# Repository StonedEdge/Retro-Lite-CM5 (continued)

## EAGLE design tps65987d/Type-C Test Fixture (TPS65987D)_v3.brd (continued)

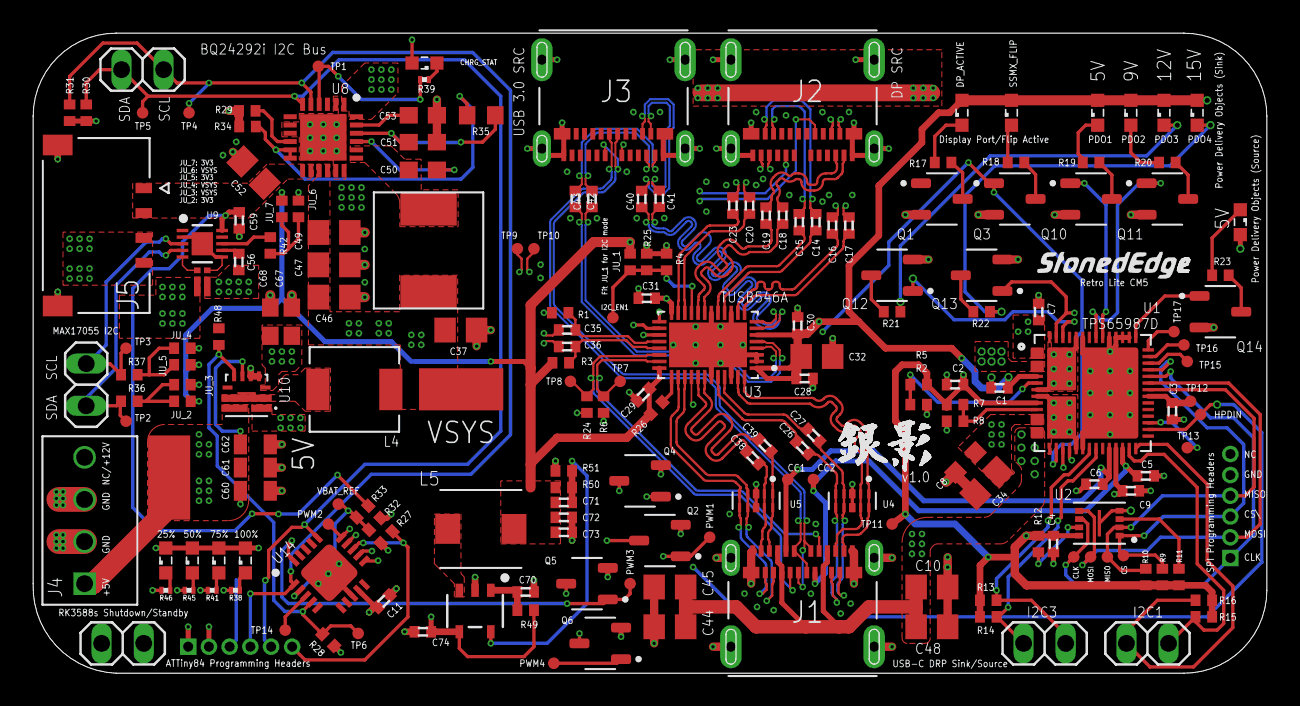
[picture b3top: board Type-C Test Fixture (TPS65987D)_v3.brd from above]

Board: 6 copper layers, 74.4 x 38.6 mm, 193 parts (0 on the bottom side), 124 nets.

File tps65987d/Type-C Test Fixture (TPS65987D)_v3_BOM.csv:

Qty,Value,Device,Package,Designator ,Description,Digikey/Mouser Link,
11,N/A,LEDSML0603,SML0603,"25%, 50%, 75%, 100%, CHRG_STAT, PDO1, PDO1_SRC1, PDO2, PDO3, PDO4, SSMX_DP_ACTIVE1",Blue LED,https://www.digikey.jp/en/products/detail/liteon/LTST-C193TB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,
5,N/A,PINHD-1X2,1X02,"JP1, JP2, JP3, JP4, JP5",PIN HEADER,https://www.digikey.jp/en/products/detail/te-connectivity-am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,
7,0 ohm,R-EU_R0402,R0402,"JU_1, JU_2, JU_3, JU_4, JU_5, JU_6, JU_7",Resistor,https://www.digikey.jp/en/products/detail/stackpole-electron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,
1,0.047µF,C-EUC0603,C0603,C50,Capacitor,https://www.digikey.jp/en/products/detail/kyocera-avx/KGM15B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,
1,0.1uF,C-EUC0402,C0402,C4,Capacitor,https://www.digikey.jp/en/products/detail/samsung-electro-me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,
3,0.1uF,C-EUC0402,C0402,"C11, C59, C70",Capacitor,https://www.digikey.jp/en/products/detail/samsung-electro-me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,
1,0.47uF,C-EUC0402,C0402,C56,Capacitor,https://www.digikey.jp/en/products/detail/samsung-electro-me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,
1,1.0uF,1.0UF-0603-16V-10%,C0603,C67,Capacitor,https://www.digikey.jp/en/products/detail/samsung-electro-me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,
2,100K,R-EU_R0402,R0402,"R1, R3",Resistor,https://www.digikey.jp/en/products/detail/yageo/RC0402FR-071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,
3,100k 1%,R-EU_R0402,R0402,"R2, R7, R8",Resistor,https://www.digikey.jp/en/products/detail/yageo/RC0402FR-071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,
18,100nF,C-EUC0402,C0402,"C14, C15, C16, C17, C18, C19, C20, C23, C28, C29, C30, C31, C35, C36, C40, C41, C42, C43",Capacitor,https://www.digikey.jp/en/products/detail/samsung-electro-me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,
1,100nF,C-EUC0402,C0402,C73,Capacitor,https://www.digikey.jp/en/products/detail/samsung-electro-me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,
1,100pF,C-EUC0402,C0402,C71,Capacitor,https://www.digikey.jp/en/products/detail/murata-electronics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,
3,N/A,105450-0101,MOLEX_105450-0101,"J1, J2, J3",USB-C Female Receptacle,https://www.digikey.jp/en/products/detail/molex/1054500101/5843890,
2,10K,R-EU_R0402,R0402,"R4, R26",Resistor,https://www.digikey.jp/en/products/detail/bourns-inc/CR0402-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,
11,10k,R-EU_R0402,R0402,"R17, R18, R19, R20, R21, R22, R23, R25, R28, R32, R49",Resistor,https://www.digikey.jp/en/products/detail/stackpole-electron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,
4,10k,R-US_R0201,R0201,"R38, R41, R45, R46",Resistor,https://www.digikey.jp/en/products/detail/stackpole-electron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,
1,10kΩ,R-EU_R0402,R0402,R34,Resistor,https://www.digikey.jp/en/products/detail/stackpole-electron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,
1,10kΩ,R-EU_R0603,R0603,R35,Resistor,,
4,10nF,C-EUC0805,C0805,"C10, C44, C45, C48",Capacitor,https://www.digikey.jp/en/products/detail/kemet/C0805X103K1R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,
1,10uF,1.0UF-0603-16V-10%,C0603,C68,Capacitor,https://www.digikey.jp/en/products/detail/samsung-electro-me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,
3,10uF,C-EUC0402,C0402,"C1, C2, C7",Capacitor,https://www.digikey.jp/en/products/detail/murata-electronics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,
2,10uF,C-EUC0402,C0402,"C72, C74",Capacitor,,
1,10uF,C-EUC0805,C0805,C32,Capacitor,,
5,10µF,C-EUC0805,C0805,"C37, C46, C47, C49, C52",Capacitor,,
1,120k 1%,R-EU_R0402,R0402,R5,Resistor,,
2,1M,R-EU_R0402,R0402,"R44, R48",Resistor,,
2,1uF,C-EUC0603,C0603,"C51, C53",Capacitor,,
1,1uH,SPM5020T-1R0M,IND_SPM5020T-1R0M,L4,Inductor,,
1,1µF,C-EUC0805,C0805,C34,Capacitor,,
1,2.2k,R-US_R0201,R0201,R39,Resistor,https://www.digikey.jp/en/products/detail/walsin-technology-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,
4,220nF,C-EUC0402,C0402,"C26, C27, C38, C39",Capacitor,,
2,220pF,C-EUC0402,C0402,"C5, C6",Capacitor,https://www.digikey.jp/en/products/detail/walsin-technology-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,
3,22uF,C-EUC0805,C0805,"C60, C61, C62",Capacitor,https://www.digikey.jp/en/products/detail/kemet/C0805C224K5R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,
1,22uF,C-EUC0402,C0402,C9,Capacitor,,
1,232k,R-EU_R0402,R0402,R50,Resistor,https://www.digikey.jp/en/products/detail/yageo/RC0402FR-072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,
1,261Ω,R-EU_R0402,R0402,R29,Resistor,https://www.digikey.jp/en/products/detail/yageo/RC0402FR-072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,
1,27.4k,R-EU_R0402,R0402,R33,Resistor,https://www.digikey.jp/en/products/detail/yageo/RC0402FR-072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,
2,2M,R-EU_R0402,R0402,"R6, R24",Resistor,https://www.digikey.jp/en/products/detail/stackpole-electron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,
4,3.3k,R-EU_R0402,R0402,"R9, R10, R11, R12",Resistor,https://www.digikey.jp/en/products/detail/walsin-technology-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,
1,332k,R-EU_R0402,R0402,R43,Resistor,https://www.digikey.jp/en/products/detail/stackpole-electron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,
10,4.7k,R-EU_R0402,R0402,"R13, R14, R15, R16, R27, R30, R31, R36, R37, R42",Resistor,https://www.digikey.jp/en/products/detail/yageo/RC0402FR-074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,
1,4.7uF,C-EUC0402,C0402,C3,Capacitor,https://www.digikey.jp/en/products/detail/samsung-electro-me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,
1,47uF,C-EUC0603,C0603,C8,Capacitor,,
1,N/A,5040500491,MOLEX_5040500491,J5,Connector,https://www.digikey.jp/en/products/detail/molex/5040500491/4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,
1,51k,R-EU_R0402,R0402,R51,Resistor,https://www.digikey.jp/en/products/detail/stackpole-electron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,
1,N/A,XIAO_4PIN_2D54,XIAO_4PIN_2D54,J4,Connector,,
2,N/A,6PINEADER,1MM_PIC-PROGRAMING_HEADER,"U$3, U$5",Programming Header,N/A,
1,AMDLA4530S-2R2MT,AMDLA4530S-2R2MT,IND_AMDLA4530S-2R2MT,L5,Inductor,https://www.digikey.jp/en/products/detail/abracon-llc/AMDLA4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,
11,N/A,AO3400A,SOT95P280X125-3N,"Q1, Q2, Q3, Q4, Q5, Q6, Q10, Q11, Q12, Q13, Q14",Transistor,https://www.digikey.jp/en/products/detail/alpha-omega-semico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,
1,N/A,ASPI-0630HI,ASPI-0630HI,L1,Inductor,https://www.digikey.jp/en/products/detail/abracon-llc/ASPI-0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,
1,N/A,BQ24292I,QFN50P400X400X100-25N,U8,Integrated Circuit,https://www.digikey.jp/en/products/detail/texas-instruments/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,
1,N/A,MAX17055ETB+T,21-100013A_T102A2+1C_MXM,U9,Integrated Circuit,https://www.digikey.jp/en/products/detail/analog-devices-inc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,
1,N/A,MCU-ATTINY84A-MU(QFN20),QFN20G-0.5-4X4MM,U14,Integrated Circuit,https://www.digikey.jp/en/products/detail/microchip-technolo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,
1,N/A,PS0306DRF7T0R01L,PS0306DRF7T0R01L,R40,,https://www.digikey.jp/en/products/detail/yageo/PS0306DRF7T0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,
1,SSMX_FLIP,LEDSML0603,SML0603,SSMX_FLIP_ACTIVE1,Blue LED,https://www.digikey.jp/en/products/detail/liteon/LTST-C193TB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,
1,SY8089AAACSY8089AAAC_SGY-L,SY8089AAACSY8089AAAC_SGY-L,SY8089AAAC_SGY-L,U13,Buck Regulator,https://www.lcsc.com/product-detail/DC-DC-Converters_Silergy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,
2,TPD4E05U06DQAR,TPD4E05U06DQAR,IC_TPD4E05U06DQAR,"U4, U5",Diode,https://www.digikey.jp/en/products/detail/texas-instruments/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,
1,TPS61235PRWLT,TPS61235PRWLT,CONV_TPS61235PRWLT,U10,Boost Regulator,https://www.digikey.jp/en/products/detail/texas-instruments/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,
1,TPS65987DDHRSHR,TPS65987DDHRSHR,IC_TPS65987DDHRSHR,U1,Integrated Circuit,https://www.digikey.jp/en/products/detail/texas-instruments/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,
1,TUSB546-DCIRNQT,TUSB546-DCIRNQT,QFN40P400X600X80-41N,U3,Integrated Circuit,https://www.digikey.jp/en/products/detail/texas-instruments/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,
1,W25X05CLUXIGTR,W25X05CLUXIGTR,PSON50P300X200X60-9N,U2,SPI Flash Memory,https://www.digikey.jp/en/products/detail/winbond-electronic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,
1,434133025816 ,434133025816 ,434133025816 ,S1,Button,,

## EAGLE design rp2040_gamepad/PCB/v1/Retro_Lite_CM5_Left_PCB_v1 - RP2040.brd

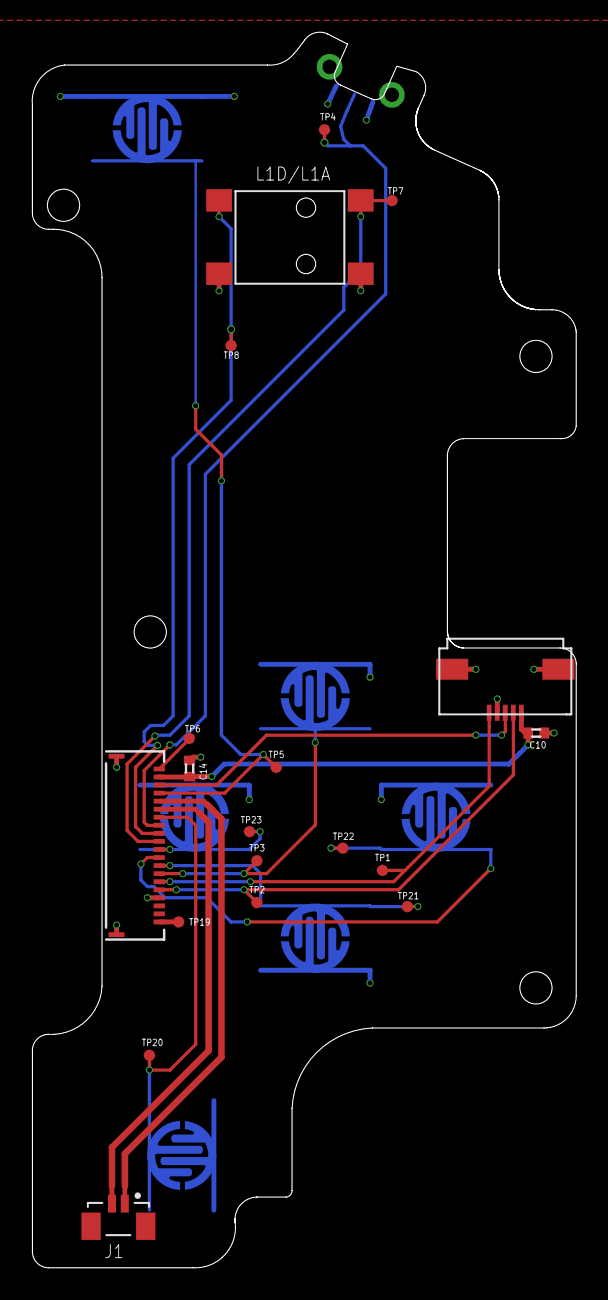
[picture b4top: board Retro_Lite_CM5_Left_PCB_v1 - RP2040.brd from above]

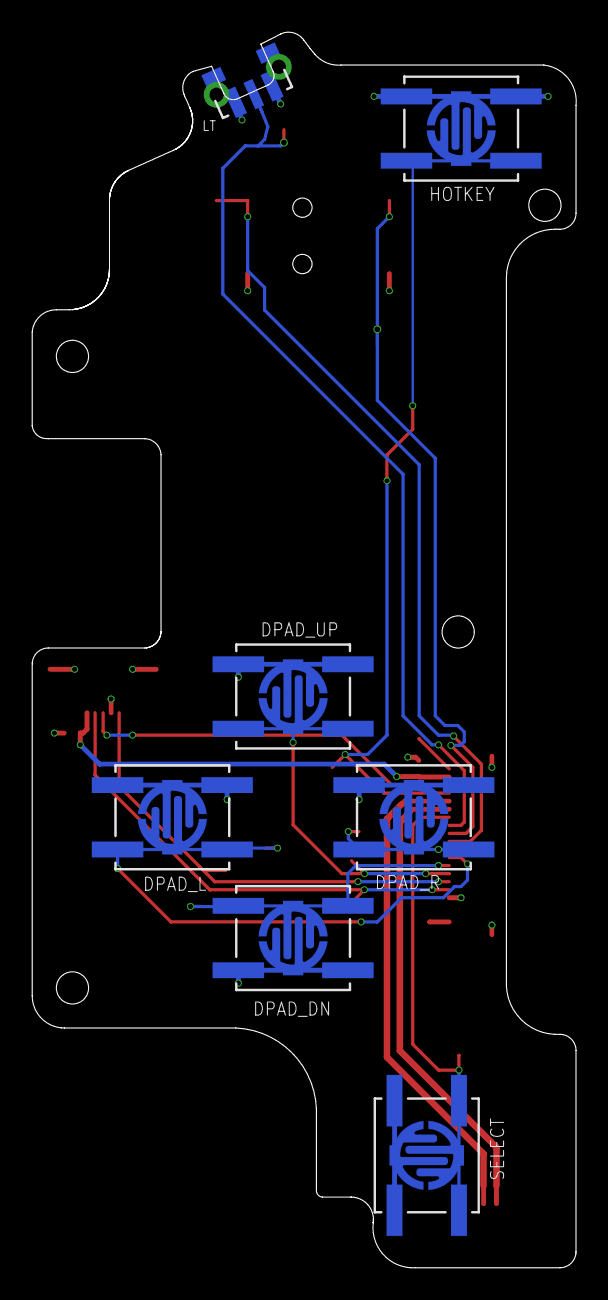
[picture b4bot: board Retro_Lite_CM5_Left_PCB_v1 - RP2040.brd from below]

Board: 2 copper layers, 33.8 x 76.7 mm, 32 parts (13 on the bottom side), 18 nets.

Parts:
C10, C14: 0.1uF; C0402
DPAD_DN: EVQ-Q2B03W; EVQQ2_3
DPAD_L: EVQ-Q2B03W; EVQQ2_3
DPAD_R: EVQ-Q2B03W; EVQQ2_3
DPAD_UP, DPAD_UP1: EVQ-Q2B03W; EVQQ2_3
HOTKEY: MEMBRANEBUTTON
J1: BM02B-SURS-TF(LF)(SN); JST_BM02B-SURS-TF(LF)(SN)
J2: 5034802000; CON_5034802000_MOL
J3: 436333033816; CONN3_3033816_WRE
SELECT: EVQ-Q2B03W; EVQQ2_3
TP1, TP2, TP3, TP4, TP5, TP6, TP7, TP8, TP19, TP20, TP21, TP22, TP23: TPTP07R; TP07R
U$1, U$2, U$3, U$4, U$5: MEMBRANEBUTTON
U$7: SWITCHSTICK_BREAKOUT
U$8: TMHF07

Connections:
3V3: C10.1, C14.2, J2.2, U$7.1
GND: C10.2, C14.1, DPAD_DN.1, DPAD_DN.4, DPAD_L.1, DPAD_L.4, DPAD_R.1, DPAD_R.4, DPAD_UP.1, DPAD_UP.4, DPAD_UP1.1, DPAD_UP1.4, HOTKEY.P$1, J1.S1, J1.S2, J2.17, J2.P1, J2.P2, J3.1, J3.3, SELECT.1, SELECT.4, U$1.P$1, U$2.P$1, U$3.P$1, U$4.P$1, U$5.P$1, U$7.4, U$7.SHIELD, U$7.SHIELD1, U$8.P$1, U$8.P$2
GPIO10/LT: J2.8, J3.2, TP4.TP
GPIO11/SELECT: J2.7, SELECT.2, SELECT.3, TP20.TP, U$5.P$2
GPIO12/DPAD_UP: DPAD_UP.2, DPAD_UP.3, J2.14, TP3.TP, U$1.P$2
GPIO13/DPAD_DOWN: DPAD_DN.2, DPAD_DN.3, J2.13, TP21.TP, U$2.P$2
GPIO14/DPAD_LEFT: DPAD_L.2, DPAD_L.3, J2.12, TP22.TP, U$3.P$2
GPIO15/DPAD_RIGHT: DPAD_R.2, DPAD_R.3, J2.11, TP23.TP, U$4.P$2
GPIO16/HOTKEY2: DPAD_UP1.2, DPAD_UP1.3, HOTKEY.P$2, J2.4, TP5.TP
GPIO20/ZL_HALF: J2.10, TP7.TP, U$8.P$3
GPIO21/ZL_FULL: J2.9, TP8.TP, U$8.P$4
GPIO23/L3: J2.3, U$7.3
GPIO28/ADC2: J2.16, TP2.TP, U$7.2
GPIO29/ADC3: J2.15, TP1.TP, U$7.5
SPK_LN: J1.1, J2.5
SPK_LP: J1.2, J2.6
TP6: J2.1, TP6.TP
VCC_5V: J2.20, TP19.TP

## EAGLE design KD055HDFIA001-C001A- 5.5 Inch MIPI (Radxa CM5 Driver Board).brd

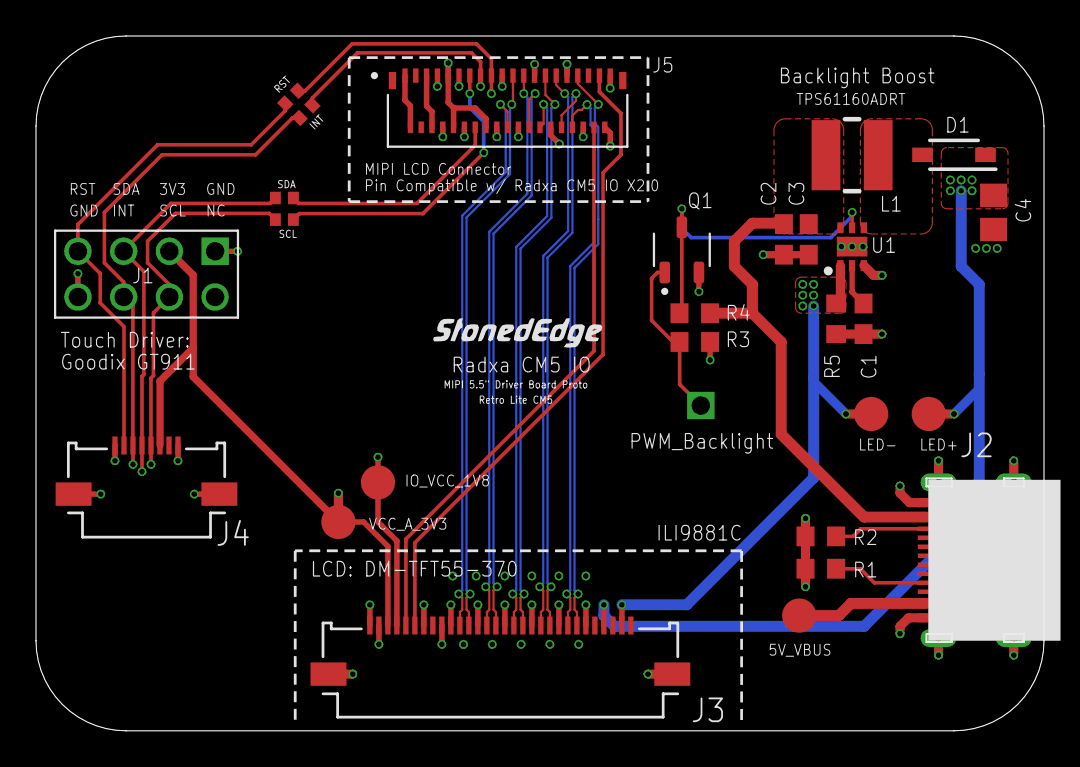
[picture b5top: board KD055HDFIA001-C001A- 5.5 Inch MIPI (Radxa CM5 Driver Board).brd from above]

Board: 4 copper layers, 56.0 x 38.6 mm, 28 parts (0 on the bottom side), 30 nets.

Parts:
5V_VBUS: TPTP19R; TP19R
C1: 220nF; C0603
C2, C3: 1µF; C0603
C4: 4.7µF 50v; C0805
D1: MBR0540T1G; SOD3716X135N
IO_VCC_1V8: TPTP19R; TP19R
J1: 10129381-908001BLF; AMPHENOL_10129381-908001BLF
J2: U262-161N-4BVC11
J3: 5051103091; CON_5051103091_MOL
J4: 5051100892; CON_5051100892_MOL
J5: FH35C-39S-0.3SHW(50); HRS_FH35C-39S-0.3SHW(50)
L1: 22µH; VLCF4020_1
LED+: TPTP19R; TP19R
LED-: TPTP19R; TP19R
Q1: AO3400A; SOT95P280X125-3N
R1: 5.1K; R0603
R2: 5.1k; R0603
R3, R4: 10k; R0603
R5: 5Ω; R0603
R6, R7, R8, R23: 0M; R0402
U1: TPS61160ADRVT; SON65P200X200X80-7N
U$1: PAD; AMPHENOL_10129381-908001BLF
VCC_A_3V3: TPTP19R; TP19R

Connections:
5V_VBUS: 5V_VBUS.TP, C2.1, C3.1, J2.A4B9, J2.B4A9, L1.1, R4.2, U1.6
CC1: J2.A5, R1.1
CC2: J2.B5, R2.1
GND: C1.1, C2.2, C3.2, C4.2, J1.01, J1.08, J2.A1B12, J2.B1A12, J2.SHIELD_1, J2.SHIELD_2, J2.SHIELD_3, J2.SHIELD_4, J3.1, J3.2, J3.7, J3.9, J3.10, J3.13, J3.16, J3.19, J3.22, J3.25, J3.P1, J3.P2, J4.1, J4.8, J4.P1, J4.P2, J5.7, J5.8, J5.11, J5.12, J5.18, J5.19, J5.22, J5.25, J5.28, J5.31, J5.34, Q1.2, R1.2, R2.2, R3.2, R5.2, U1.3, U1.7
GPIO_PWM: Q1.1, R3.1, U$1.01
I2C_SCL_TP: J1.04, J4.5, J5.13, R23.1, R23.2
I2C_SDA_TP: J1.05, J4.4, J5.14, R7.1, R7.2
IO_VCC_1V8: IO_VCC_1V8.TP, J3.4, J5.38
LCD_RESET: J3.5, J5.36
LED+: C4.1, D1.1, J3.27, LED+.TP
LED-: J3.29, LED-.TP, R5.1, U1.1
MIPI_CL_N: J3.18, J5.27
MIPI_CL_P: J3.17, J5.26
MIPI_D0_N: J3.24, J5.33
MIPI_D0_P: J3.23, J5.32
MIPI_D1_N: J3.21, J5.30
MIPI_D1_P: J3.20, J5.29
MIPI_D2_N: J3.15, J5.24
MIPI_D2_P: J3.14, J5.23
MIPI_D3_N: J3.12, J5.21
MIPI_D3_P: J3.11, J5.20
MIPI_TE: J3.6, J5.37
unnamed: C1.2, U1.2
unnamed: D1.2, L1.2, U1.4
unnamed: Q1.3, R4.1, U1.5
TP_INT: J1.06, J4.3, J5.15, R6.1, R6.2
TP_RESET: J1.07, J4.2, J5.17, R8.1, R8.2
VCC_A_3V3: J1.03, J3.3, J4.6, J5.9, J5.10, J5.16, J5.39, VCC_A_3V3.TP
VCC_LEDA_NC: J5.1, J5.2
VCC_LEDK_NC: J5.5, J5.6

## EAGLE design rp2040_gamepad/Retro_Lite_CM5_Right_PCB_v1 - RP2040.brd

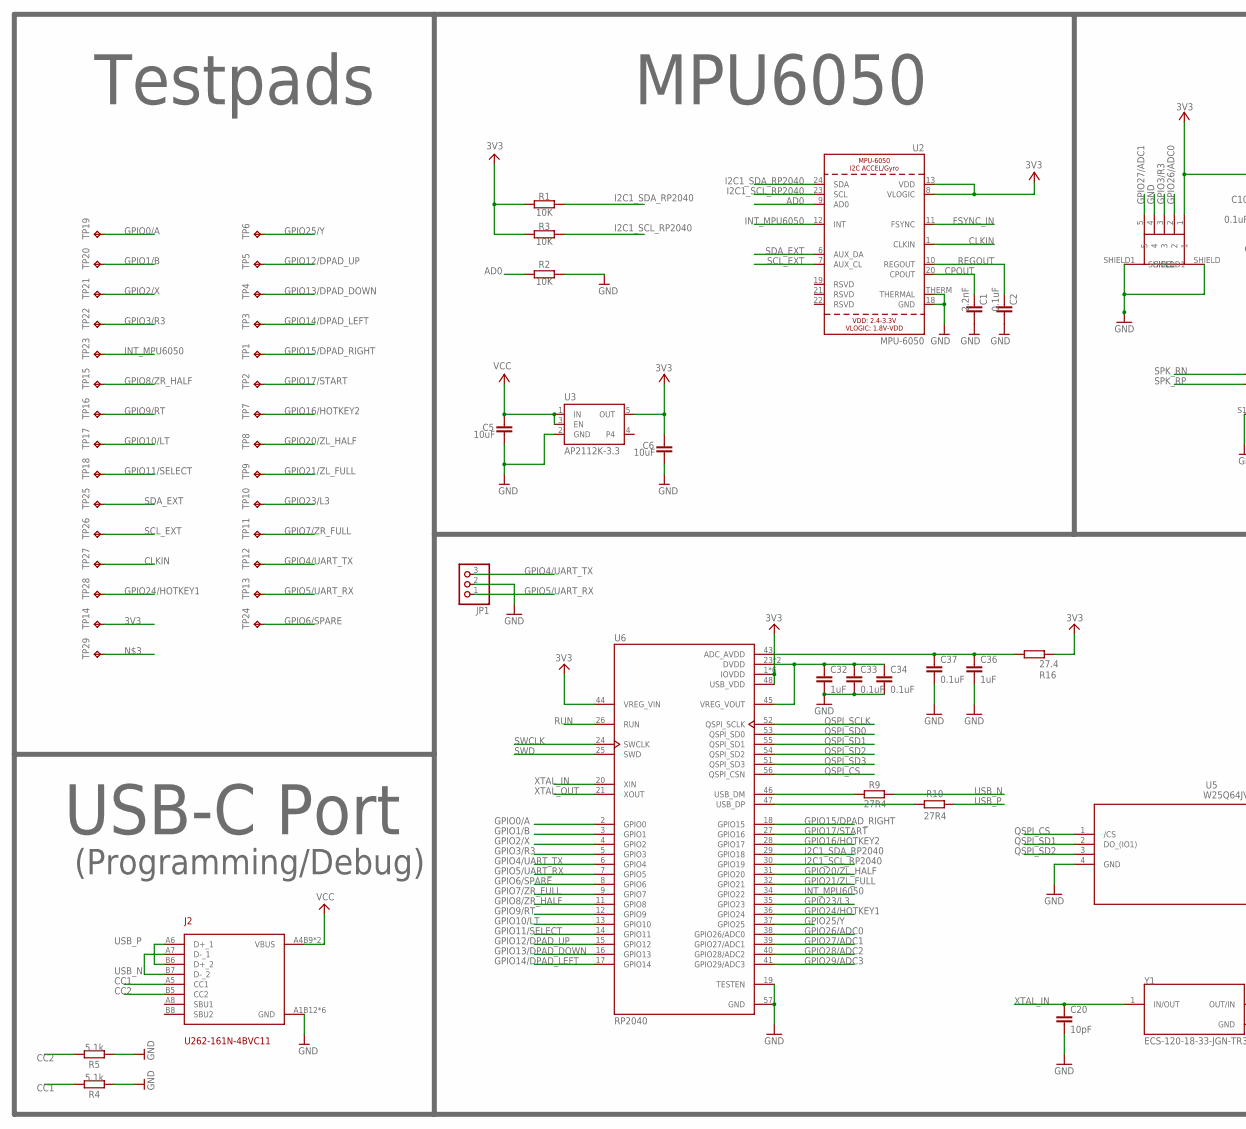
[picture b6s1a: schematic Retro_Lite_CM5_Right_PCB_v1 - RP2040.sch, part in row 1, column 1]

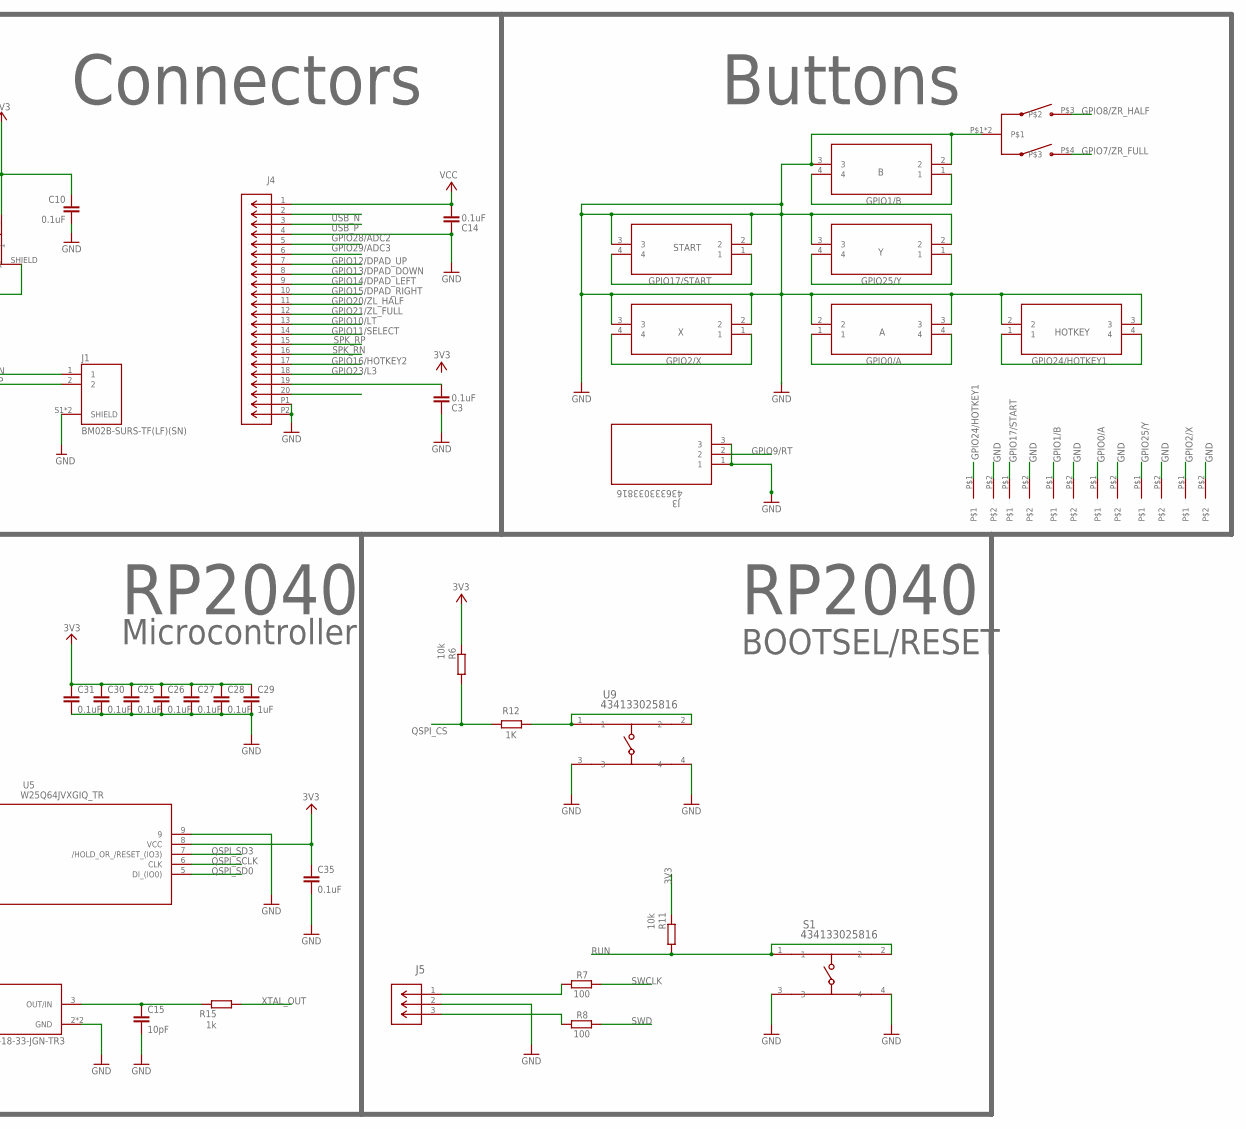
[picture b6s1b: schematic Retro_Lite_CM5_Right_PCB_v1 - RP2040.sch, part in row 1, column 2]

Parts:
A: A; EVQQ2_3
AA: MEMBRANEBUTTON
B: B; EVQQ2_3
BB: MEMBRANEBUTTON
C1: 2.2nF; C0402
C2, C3, C10, C14, C25, C26, C27, C28, C30, C31, C33, C34, C35, C37: 0.1uF; C0402
C5, C6: 10uF; C0402
C15, C20: 10pF; C0402
C29, C32, C36: 1uF; C0402
HOTKEY: A; EVQQ2_3
J1: BM02B-SURS-TF(LF)(SN); JST_BM02B-SURS-TF(LF)(SN)
J2: U262-161N-4BVC11
J3: 436333033816; CONN3_3033816_WRE
J4: 5034802000; CON_5034802000_MOL
J5: BM03B-SRSS-TB(LF)(SN); CONN_BM03B-SRSS-TB(LF)(SN)_JST
JP1: PINHD-1X3; 1X03
R1, R2, R3: 10K; R0402
R4, R5: 5.1k; R0402
R6, R11: 10k; R0402
R7, R8: 100; R0402
R9, R10: 27R4; R0402
R12: 1K; R0402
R15: 1k; R0402
R16: 27.4; R0402
S1: 434133025816; SMD_025816_WRE
START: START; EVQQ2_3
START1: MEMBRANEBUTTON
T1: MEMBRANEBUTTON
TP1, TP2, TP3, TP4, TP5, TP6, TP7, TP8, TP9, TP10, TP11, TP12, TP13, TP14, TP15, TP16, TP17, TP18, TP19, TP20, TP21, TP22, TP23, TP24, TP25, TP26, TP27, TP28, TP29: TPTP07R; TP07R
U2: MPU-6050; QFN24_4MM_SMSC
U3: AP2112K-3.3; SOT23-5
U5: W25Q64JVXGIQ_TR; DFN_XGIQ_TR_WIN
U6: RP2040; QFN40P700X700X90-57N
U9: 434133025816; SMD_025816_WRE
U$1: SWITCHSTICK_BREAKOUT
U$2: TMHF07
X: X; EVQQ2_3
XX: MEMBRANEBUTTON
Y: Y; EVQQ2_3
Y1: ECS-120-18-33-JGN-TR3; XTAL_ECS-120-18-33-JGN-TR3
YY: MEMBRANEBUTTON

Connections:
3V3: C3.2, C6.1, C10.1, C25.1, C26.1, C27.1, C28.1, C29.1, C30.1, C31.1, C35.1, J4.19, R1.1, R3.1, R6.2, R11.2, R16.2, TP14.TP, U2.8 (VLOGIC), U2.13 (VDD), U3.5 (OUT), U5.8 (VCC), U6.1 (IOVDD), U6.10 (IOVDD), U6.22 (IOVDD), U6.33 (IOVDD), U6.42 (IOVDD), U6.44 (VREG_VIN), U6.48 (USB_VDD), U6.49 (IOVDD), U$1.1
AD0: R2.1, U2.9 (AD0)
CC1: J2.A5 (CC1), R4.2
CC2: J2.B5 (CC2), R5.2
CLKIN: TP27.TP, U2.1 (CLKIN)
CPOUT: C1.1, U2.20 (CPOUT)
FSYNC_IN: U2.11 (FSYNC)
GND: A.2, A.3, AA.P$2, B.2, B.3, BB.P$2, C1.2, C2.2, C3.1, C5.2, C6.2, C10.2, C14.1, C15.2, C20.2, C25.2, C26.2, C27.2, C28.2, C29.2, C30.2, C31.2, C32.2, C33.2, C34.2, C35.2, C36.2, C37.2, HOTKEY.2, HOTKEY.3, J1.S1 (SHIELD), J1.S2 (SHIELD), J2.A1B12 (GND), J2.B1A12 (GND), J2.SHIELD_1 (GND), J2.SHIELD_2 (GND), J2.SHIELD_3 (GND), J2.SHIELD_4 (GND), J3.1, J3.3, J4.4, J4.P1, J4.P2, J5.2, JP1.2, R2.2, R4.1, R5.1, S1.3, S1.4, START.2, START.3, START1.P$2, T1.P$2, U2.18 (GND), U2.THERM (THERMAL), U3.2 (GND), U5.4 (GND), U5.9, U6.19 (TESTEN), U6.57 (GND), U9.3, U9.4, U$1.4, U$1.SHIELD, U$1.SHIELD1, U$2.P$1, U$2.P$2, X.2, X.3, XX.P$2, Y.2, Y.3, Y1.2 (GND), Y1.4 (GND), YY.P$2
GPIO0/A: A.1, A.4, AA.P$1, TP19.TP, U6.2 (GPIO0)
GPIO1/B: B.1, B.4, BB.P$1, TP20.TP, U6.3 (GPIO1)
GPIO2/X: TP21.TP, U6.4 (GPIO2), X.1, X.4, XX.P$1
GPIO3/R3: TP22.TP, U6.5 (GPIO3), U$1.3
GPIO4/UART_TX: JP1.3, TP12.TP, U6.6 (GPIO4)
GPIO5/UART_RX: JP1.1, TP13.TP, U6.7 (GPIO5)
GPIO6/SPARE: TP24.TP, U6.8 (GPIO6)
GPIO7/ZR_FULL: TP11.TP, U6.9 (GPIO7), U$2.P$4
GPIO8/ZR_HALF: TP15.TP, U6.11 (GPIO8), U$2.P$3
GPIO9/RT: J3.2, TP16.TP, U6.12 (GPIO9)
GPIO10/LT: J4.13, TP17.TP, U6.13 (GPIO10)
GPIO11/SELECT: J4.14, TP18.TP, U6.14 (GPIO11)
GPIO12/DPAD_UP: J4.7, TP5.TP, U6.15 (GPIO12)
GPIO13/DPAD_DOWN: J4.8, TP4.TP, U6.16 (GPIO13)
GPIO14/DPAD_LEFT: J4.9, TP3.TP, U6.17 (GPIO14)
GPIO15/DPAD_RIGHT: J4.10, TP1.TP, U6.18 (GPIO15)
GPIO16/HOTKEY2: J4.17, TP7.TP, U6.28 (GPIO17)
GPIO17/START: START.1, START.4, START1.P$1, TP2.TP, U6.27 (GPIO16)
GPIO20/ZL_HALF: J4.11, TP8.TP, U6.31 (GPIO20)
GPIO21/ZL_FULL: J4.12, TP9.TP, U6.32 (GPIO21)
GPIO23/L3: J4.18, TP10.TP, U6.35 (GPIO23)
GPIO24/HOTKEY1: HOTKEY.1, HOTKEY.4, T1.P$1, TP28.TP, U6.36 (GPIO24)
GPIO25/Y: TP6.TP, U6.37 (GPIO25), Y.1, Y.4, YY.P$1
GPIO26/ADC0: U6.38 (GPIO26/ADC0), U$1.2
GPIO27/ADC1: U6.39 (GPIO27/ADC1), U$1.5
GPIO28/ADC2: J4.5, U6.40 (GPIO28/ADC2)
GPIO29/ADC3: J4.6, U6.41 (GPIO29/ADC3)
I2C1_SCL_RP2040: R3.2, U2.23 (SCL), U6.30 (GPIO19)
I2C1_SDA_RP2040: R1.2, U2.24 (SDA), U6.29 (GPIO18)
INT_MPU6050: TP23.TP, U2.12 (INT), U6.34 (GPIO22)
unnamed: C15.1, R15.2, Y1.3 (OUT/IN)
unnamed: J5.1, R7.1
unnamed: J4.20, TP29.TP
unnamed: J5.3, R8.1
unnamed: C32.1, C33.1, C34.1, U6.23 (DVDD), U6.45 (VREG_VOUT), U6.50 (DVDD)
unnamed: R9.2, U6.46 (USB_DM)
unnamed: R10.2, U6.47 (USB_DP)
unnamed: R12.1, U9.1, U9.2
unnamed: C36.1, C37.1, R16.1, U6.43 (ADC_AVDD)
QSPI_CS: R6.1, R12.2, U5.1 (/CS), U6.56 (QSPI_CSN)
QSPI_SCLK: U5.6 (CLK), U6.52 (QSPI_SCLK)
QSPI_SD0: U5.5 (DI_(IO0)), U6.53 (QSPI_SD0)
QSPI_SD1: U5.2 (DO_(IO1)), U6.55 (QSPI_SD1)
QSPI_SD2: U5.3 (/WP_(IO2)), U6.54 (QSPI_SD2)
QSPI_SD3: U5.7 (/HOLD_OR_/RESET_(IO3)), U6.51 (QSPI_SD3)
REGOUT: C2.1, U2.10 (REGOUT)
RUN: R11.1, S1.1, S1.2, U6.26 (RUN)
SCL_EXT: TP26.TP, U2.7 (AUX_CL)
SDA_EXT: TP25.TP, U2.6 (AUX_DA)
SPK_RN: J1.1, J4.16
SPK_RP: J1.2, J4.15
SWCLK: R7.2, U6.24 (SWCLK)
SWD: R8.2, U6.25 (SWD)
USB_N: J2.A7 (D-_1), J2.B7 (D-_2), J4.2, R9.1
USB_P: J2.A6 (D+_1), J2.B6 (D+_2), J4.3, R10.1
VCC: C5.1, C14.2, J2.A4B9 (VBUS), J2.B4A9 (VBUS), J4.1, U3.1 (IN), U3.3 (EN)
XTAL_IN: C20.1, U6.20 (XIN), Y1.1 (IN/OUT)
XTAL_OUT: R15.1, U6.21 (XOUT)

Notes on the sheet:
MPU6050
RP2040
Buttons
Connectors
USB-C Port
Testpads
(Programming/Debug)
Microcontroller
BOOTSEL/RESET

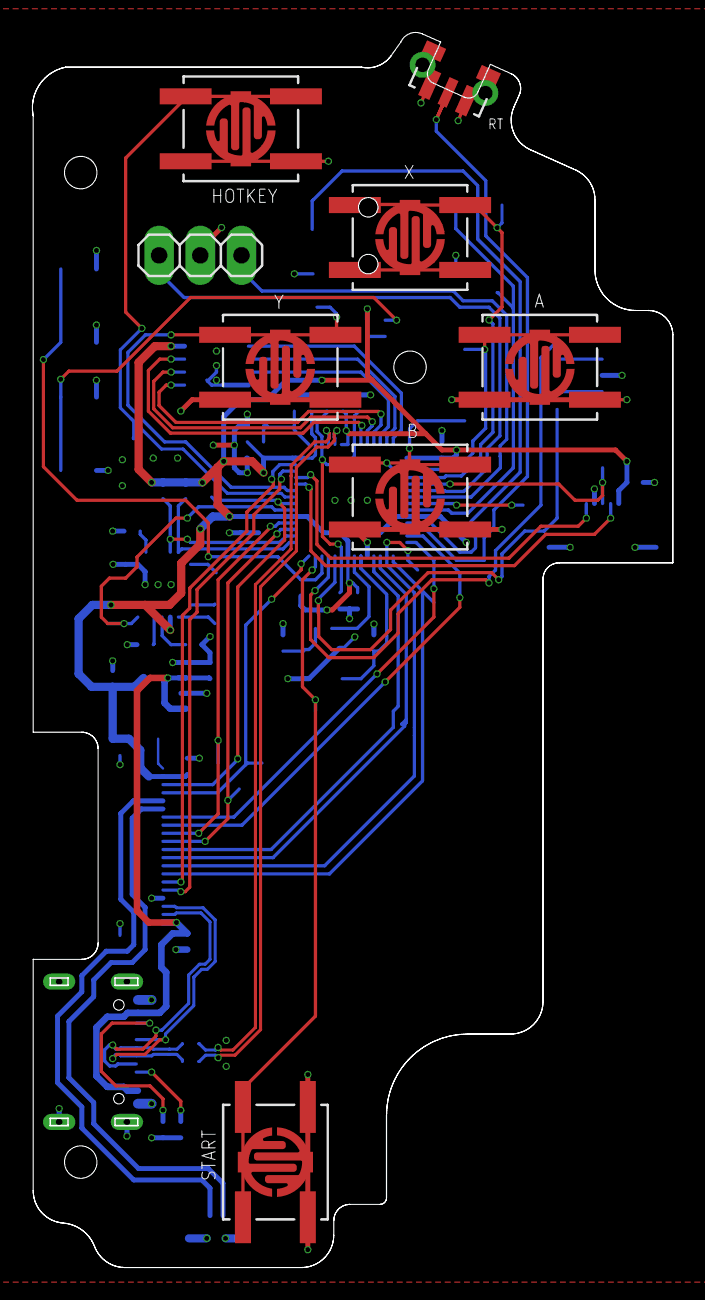
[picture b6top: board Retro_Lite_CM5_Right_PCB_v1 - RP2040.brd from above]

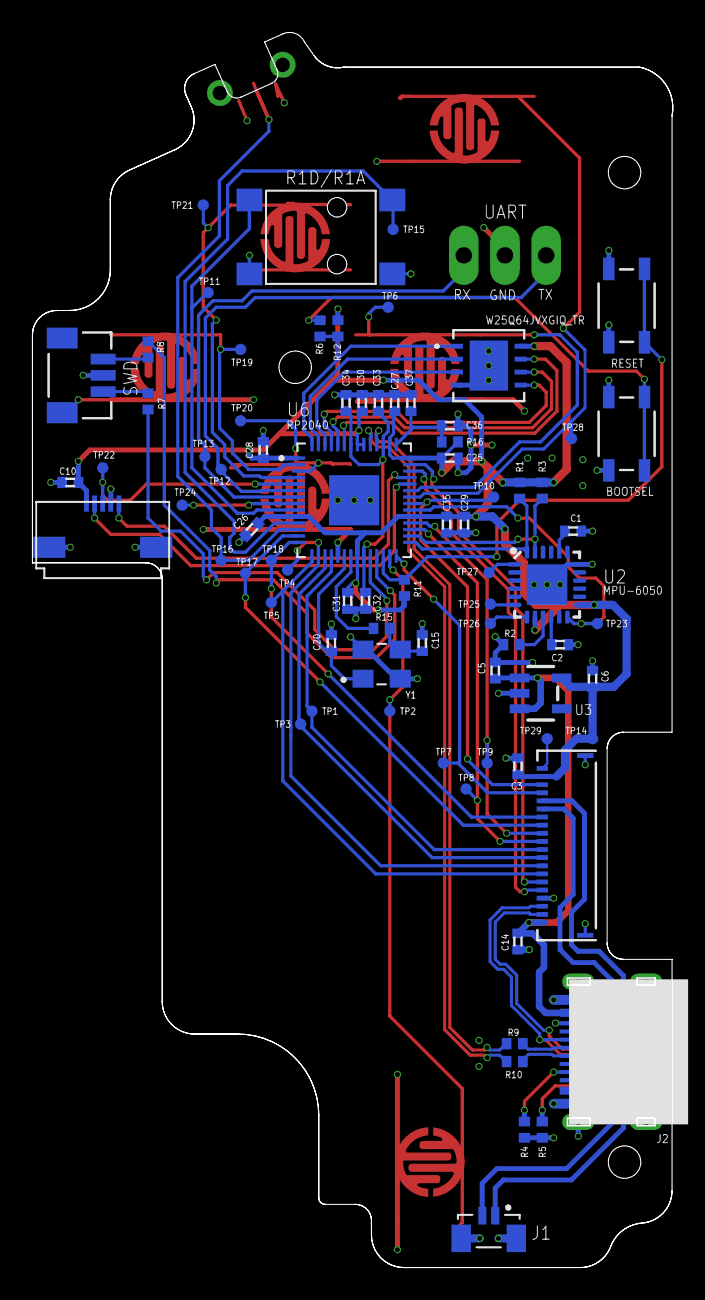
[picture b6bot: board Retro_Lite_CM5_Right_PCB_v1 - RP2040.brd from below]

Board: 2 copper layers, 39.5 x 76.1 mm, 92 parts (78 on the bottom side), 65 nets.

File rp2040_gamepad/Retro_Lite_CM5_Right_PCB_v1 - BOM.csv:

Part Value/No,Designator,Quantity,Unit Price,Total,Footprint,Source Link
0.1uF,C2 C3 C10 C14 C25 C26 C27 C28 C30 C31 C33 C34 C35 C37,50,0.0054,0.27,C0402,https://www.digikey.jp/en/products/detail/samsung-electro-me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
1K,R12 R15,10,0.015,0.15,R0402,https://www.digikey.jp/en/products/detail/yageo/RC0402FR-071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
1uF,C29 C32 C36,10,0.017,0.17,C0402,https://www.digikey.jp/en/products/detail/samsung-electro-me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
2.2nF,C1,1,0.11,0.11,C0402,https://www.digikey.jp/en/products/detail/kemet/C0402C222K3G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
5.1K,R4 R5,10,0.012,0.12,R0402,https://www.digikey.jp/en/products/detail/yageo/RC0402FR-135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
10K,R1 R2 R3 R6 R11,10,0.012,0.12,R0402,https://www.digikey.jp/en/products/detail/bourns-inc/CR0402-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
10pF,C15 C20,10,0.025,0.25,C0402,https://www.digikey.jp/en/products/detail/murata-electronics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
10uF,C5 C6,10,0.019,0.19,C0402,https://www.digikey.jp/en/products/detail/murata-electronics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
274R,R9 R10 R16,10,0.015,0.15,R0402,https://www.digikey.jp/en/products/detail/yageo/RC0402FR-072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
100R,R7 R8,10,0.015,0.15,R0402,https://www.digikey.jp/en/products/detail/yageo/RC0402FR-071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
434133025816,S1 U9,2,0.54,1.08,SMD_025816_WRE,https://www.digikey.jp/en/products/detail/w%C3%BCrth-elektro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
5034802000,J4,1,1.79,1.79,CON_5034802000_MOL,https://www.digikey.jp/en/products/detail/molex/5034802000/2356628
AP2112K-3.3,U3,1,0.35,0.35,SOT23-5,https://www.digikey.jp/en/products/detail/diodes-incorporate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
BM02B-SURS-TF(LF)(SN),J1,1,0.44,0.44,JST_BM02B-SURS-TF(LF)(SN),https://www.digikey.jp/en/products/detail/jst-sales-america-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
BM03B-SRSS-TB(LF)(SN),J5,1,0.53,0.53,CONN_BM03B-SRSS-TB(LF)(SN)_JST,https://www.digikey.jp/en/products/detail/jst-sales-america-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
ECS-120-18-33-JGN-TR3,Y1,1,0.4,0.4,XTAL_ECS-120-18-33-JGN-TR3,https://www.digikey.jp/en/products/detail/ecs-inc/ECS-120-18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
MPU-6050,U2,1,8.71,8.71,QFN24_4MM_SMSC,https://www.digikey.jp/en/products/detail/tdk-invensense/MPU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
RP2040,U6,1,0.7,0.7,QFN40P700X700X90-57N,https://www.digikey.jp/en/products/detail/raspberry-pi/SC091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
5051100592,U1,1,0.7,0.7,5051100592,https://www.digikey.jp/en/products/detail/molex/5051100592/5700453
TMHF07,U2,1,0.2,0.2,TMHF07,https://www.alibaba.com/product-detail/kejian-tmhf07-6-5-6-2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
U262-161N-4BVC11,J2,1,1,1,U262-161N-4BVC11,https://www.lcsc.com/product-detail/USB-Connectors_XKB-Conne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
W25Q64JVXGIQ_TR,U5,1,1.1,1.1,DFN_XGIQ_TR_WIN,https://www.digikey.jp/en/products/detail/winbond-electronic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
EVQQ2B03W,A B X Y START ,5,0.26,1.3,EVQQ2B03W,https://www.digikey.jp/en/products/detail/panasonic-electron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
,,,Total BOM ,19.98,,

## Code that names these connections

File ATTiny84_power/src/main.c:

#include <Arduino.h>
#include "bq24292i.h"

byte power_btn = PIN_PA2;           // Power button connected to this pin. Low Active
byte sys_on = PIN_PA1;              // Regulator power. Active High
byte sht_dwn = PIN_PB0;             // Connected to GPIO25. Signal to start CM5 Shutdown. Active High
byte low_volt_shutdown = PIN_PB1;   // Connected to GPIO16 on CM5. Used for low voltage shut down

byte led1 = PIN_PB2;
byte led2 = PIN_PA7;
byte led3 = PIN_PA5;

bool lowVoltInState = false;
bool lastLowVoltInState = false;
bool systemState = false;
bool shutdownInit = false;

unsigned long powerBtnTimer;
unsigned long shutDown;
long powerOnDelay = 1000;
long powerOffDelay = 3000;
long shutDownDelay = 10000;
bool btnTimerStarted = false;
bool shutDownTimerStarted = false;

unsigned long lastLowVoltDebounce = 0;
unsigned long debounceDelay = 50;

const float R1 = 10000.0;  // Value of R1 resistor div 
const float R2 = 27400.0;  // Value of R2 resistor div
float vBatSum;
uint8_t vBatReadCounter;

float readAvgVBAT() {
    uint8_t vBatADCRaw = analogRead(A3);              // Store ADC reading
    float vBatADCVoltage = (vBatADCRaw * 1.1) / 256.0;  // Convert analog to voltage value
    float vBatAdj = vBatADCVoltage / (R2 / (R1 + R2));  // Adjust voltage for divider
    vBatSum += vBatAdj;
    vBatReadCounter++;
    return vBatSum / vBatReadCounter;
}

void BQ_INIT() {
    bq24292i_set_iin_max(BQ_IIN_MAX_3000MA);
    bq24292i_set_vin_max(5080);

    bq24292i_set_vsys_min(3500);
    bq24292i_set_charge_config(BQ_CHG_CONFIG_ENABLE);

    bq24292i_set_charge_current(2496);

    bq24292i_set_term_current(256);
    bq24292i_set_precharge_current(256);

    bq24292i_set_recharge_offset(BQ_VRECHG_100MV);
    bq24292i_set_batlow_voltage(BQ_VBATLOW_2800MV);
    bq24292i_set_max_charge_voltage(4208);

    bq24292i_set_charge_timer(BQ_CHG_TIMER_8H);
    bq24292i_set_wdt_config(BQ_WATCHDOG_DISABLE);
    bq24292i_set_charge_termination(true);

    bq24292i_set_max_temp(BQ_MAX_TEMP_80C);
    bq24292i_set_voltage_clamp(0);
    bq24292i_set_comp_resistor(0);

    bq24292i_set_interrupt_mask(BQ_INT_BAT_AND_CHRG_FAULT);
    bq24292i_set_batfet_enabled(false);
}

void lowVoltShutdownDebounce() {
    bool input = !digitalRead(low_volt_shutdown);
    if (input != lastLowVoltInState)
        lastLowVoltDebounce = millis() + debounceDelay;

    if (millis() > lastLowVoltDebounce)
        lowVoltInState = input;

    lastLowVoltInState = input;
}

void shutdownTimer() {
    if (!shutDownTimerStarted) {
        shutDown = millis() + shutDownDelay;
        shutDownTimerStarted = true;
        digitalWrite(sht_dwn, HIGH); // Tell CM5 to Shut down
        digitalWrite(led3, HIGH);
        shutdownInit = true;
    }
    else if (millis() > shutDown) {
        digitalWrite(sys_on, LOW);
        digitalWrite(sht_dwn, LOW);
        digitalWrite(led2, LOW);
        digitalWrite(led3, LOW);
        systemState = 0;
        shutDownTimerStarted = false;
        shutdownInit = false;
    }
}

void powerTimerCheck() {
    if (!btnTimerStarted) {
        btnTimerStarted = true;
        vBatReadCounter = 0;
        vBatSum = 0;
        powerBtnTimer = millis() +
            ((systemState == 0) ? powerOnDelay : powerOffDelay);
    }
    else if (millis() > powerBtnTimer) {
        btnTimerStarted = false;
        if (systemState) {
            systemState = false;
            digitalWrite(sht_dwn, HIGH);
            digitalWrite(led3, HIGH);
            shutdownInit = true;
        }
        else if (readAvgVBAT() > 3.2) { // Check battery voltage before allowing sys_on to go high
            systemState = true;
            digitalWrite(sys_on, HIGH);
            digitalWrite(led2, HIGH);
        }
        else {
            // Flash LED1 if the user presses the button down during low battery and system off state
            for (int i = 0; i < 10; i++) {
                digitalWrite(led1, HIGH);
                delay(250);
                digitalWrite(led1, LOW);
                delay(250);
            }
        }
    }
    else if (!systemState)
        readAvgVBAT();      // Keep reading voltage while button is pressed
}

void setup() {
    cli();                  // Disable interrupts
    CLKPR = (1 << CLKPCE);  // Prescaler enable
    CLKPR = 0x00;           // Clock division factor
    sei();                  // Enable interrupts
    
    pinMode(power_btn, INPUT_PULLUP);
    pinMode(sys_on, OUTPUT);
    pinMode(sht_dwn, OUTPUT);
    pinMode(low_volt_shutdown, INPUT_PULLUP);
    pinMode(led1, OUTPUT);
    pinMode(led2, OUTPUT);
    pinMode(led3, OUTPUT);

    pinMode(A3, INPUT);
    analogReference(INTERNAL);  // Setup the ADC voltage ref as 1.1V

    // Not sure if these are needed?
    ADMUX  |= (1 << ADLAR);     // Left Adjust the ADCH and ADCL registers for 8-bit resolution. No need for 10-bit
    ADCSRA |= (1 << ADEN);      // ADC enable 
    ADCSRA |= (1 << ADPS1);     // Set prescaler 
    ADCSRA |= (1 << ADPS0);     // Set division factor-8 for 1MHz ADC clock

    digitalWrite(led1, LOW);
    digitalWrite(led2, LOW);
    digitalWrite(led3, LOW);

    i2c_master_init();

    // digitalWrite(led1, bq24292i_is_present());

    BQ_INIT(); 
}

void loop() {
    bool powerBtnState = !digitalRead(power_btn);
    lowVoltShutdownDebounce();

    if (shutdownInit || lowVoltInState)
        shutdownTimer();
    else if (powerBtnState)
        powerTimerCheck();
    else
        btnTimerStarted = false;
}

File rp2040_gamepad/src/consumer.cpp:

#include "gamepad.h"

static uint16_t lastKey = 0;

uint16_t get_consumer_report(uint8_t* buffer, uint16_t reqlen)
{
    if (reqlen >= 2) {
        *(uint16_t*)buffer = 0;
        return 2;
    }

    return 0;
}

bool send_consumer_report()
{
    // Poll every 10ms
    const uint32_t interval_ms = 10;
    static uint32_t start_ms = 0;

    if (board_millis() - start_ms < interval_ms)
        return false; // not enough time
    start_ms += interval_ms;

    uint16_t key = 0;
    if (buttonState[BTN_HOTKEY_PLUS]) {
        if (dpadPinState[DPAD_UP])
            key = HID_USAGE_CONSUMER_BRIGHTNESS_INCREMENT;
        else if (dpadPinState[DPAD_DOWN])
            key = HID_USAGE_CONSUMER_BRIGHTNESS_DECREMENT;
        else if (dpadPinState[DPAD_LEFT])
            key = HID_USAGE_CONSUMER_VOLUME_DECREMENT;
        else if (dpadPinState[DPAD_RIGHT])
            key = HID_USAGE_CONSUMER_VOLUME_INCREMENT;
    }

    if (lastKey != key) {
        tud_hid_report(REPORT_ID_CONSUMER_CONTROL, &key, 2);
        lastKey = key;
        return true;
    }

    return false;
}

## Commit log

2023-08-01 To-do list extension
2023-09-10 Update README.md
    Complete display testing using Orange Pi 5
2023-10-26 Update README.md
    Progress update - WM8960 working
2023-11-06 Add initial source code for HID
2023-11-06 Remove commented-out stuff
2023-11-06 Working buttons
2023-11-06 Formatting nits
2023-11-07 Label buttons, bring back calibration
2023-11-07 Off by one
2023-11-07 Update status, add Armbian patch
2023-11-07 Update patch author
2023-11-07 Fix conflict
2023-11-07 Don't wait for Serial
2023-11-16 USB-C PD Test Fixture v1.0
2023-11-16 Remove DMP, bring back Keyboard, add Multi-Axis controller and one more button
2023-12-04 Initial framework for RP2040 (as an air mouse)
2023-12-09 Format code
2023-12-09 Fix build
2023-12-10 Send multi-axis data
2023-12-10 Update userpatch
2023-12-26 Add files via upload
    Add project test settings for generating TPS65987D flash bin
2024-01-05 RP2040 v1 alpha PCB schematics/BOM
2024-01-05 Rename rp2040_gamepad/Retro_Lite_CM5_Right_PCB_v1 - RP2040.brd to rp2040_gamepad/PCB/Retro_Lite_CM5_Right_PCB_v1 - RP2040.brd
2024-01-05 Rename rp2040_gamepad/Retro_Lite_CM5_Right_PCB_v1 - RP2040.sch to rp2040_gamepad/PCB/Retro_Lite_CM5_Right_PCB_v1 - RP2040.sch
2024-01-07 Add Type-C TPS65987D/TUSB546 PCB design files
2024-01-10 Rename Retro Lite CM5_PMS_v1_Test_Gerbers.zip to tps65987d/Retro Lite CM5_PMS_v1_Test_Gerbers.zip
2024-01-10 Rename Type-C Test Fixture (TPS65987D)_v1.brd to tps65987d/Type-C Test Fixture (TPS65987D)_v1.brd
2024-01-10 Rename Type-C Test Fixture (TPS65987D)_v1.sch to tps65987d/Type-C Test Fixture (TPS65987D)_v1.sch
2024-01-10 Rename KD055HDFIA001-C001A Datasheet.pdf to KD055HDFIA001-C001A/KD055HDFIA001-C001A Datasheet.pdf
2024-01-10 Rename KD055HDFIA001-C001A- 5.5 Inch MIPI (Radxa CM5 Driver Board) - Gerbers.zip to KD055HDFIA001-C001A/KD055HDFIA001-C001A- 5.5 Inch MIPI (Radxa CM5 Driver Board) - Gerbers.zip
2024-01-10 Rename KD055HDFIA001-C001A- 5.5 Inch MIPI (Radxa CM5 Driver Board).brd to KD055HDFIA001-C001A/KD055HDFIA001-C001A- 5.5 Inch MIPI (Radxa CM5 Driver Board).brd
2024-01-10 Rename KD055HDFIA001-C001A- 5.5 Inch MIPI (Radxa CM5 Driver Board).sch to KD055HDFIA001-C001A/KD055HDFIA001-C001A- 5.5 Inch MIPI (Radxa CM5 Driver Board).sch
2024-01-12 Fix ADCIN1 resistor div
2024-01-14 Fix brightness control, add patch for DP output
2024-01-15 Placeholder for STL files
2024-01-15 STEP file placeholder
2024-01-15 Initial (broken) placeholder for gamepad code
2024-01-15 More broken code
2024-01-15 Apply clang-format
2024-01-15 Compile success
2024-01-15 Tracking works
2024-01-15 Use flash to store calibration
2024-01-15 Enable ADC
2024-01-15 Disable mouse by default
2024-01-15 12 bit
2024-01-17 Minor fixes and formatting nits
2024-01-18 Remove delays from calibration
2024-01-29 Add v1.0 Retro Lite CM5 enclosure STLs
2024-01-29 Fix button issues
2024-01-29 Remove STL files due to errors
2024-02-06 Fix button mapping
2024-02-06 Mouse toggle should be different from calibration
2024-02-06 Fix I2C and UART
2024-02-06 Fix calibration persist
2024-02-06 Unify flash operations
2024-02-06 Tracking on demand
2024-02-07 Add USB serial
2024-02-08 Add v14 individual CM5 enclosure files
2024-02-10 Swap USB30_2_SSTX_* & USB30_2_SSRX_* lanes
2024-02-12 Add mouse calibration, swap axes
2024-02-17 Upload v3 schematic (PDF)
2024-02-19 Upload BoM
2024-02-19 Upload BoM (CSV)
2024-02-21 Fix 5V FB resistors
2024-02-21 Fix 5V feedback resistors
2024-02-22 Add ATTiny84 controller code
2024-02-22 Fix pins and timings
2024-02-23 Invert low voltage logic + pull down
2024-02-23 Add bq24292i driver copyright
2024-02-23 Use LEDs for monitoring current state
2024-02-28 Upload v1.0 CM5 carrier board
    Order at your own risk! Untested.
2024-02-28 Fix M.2 standoff hole size for 9774015243R
2024-02-28 Gib gerbers. Untested!
2024-02-28 Upload mnt (top) placement co-ordinates
2024-03-03 Add Max17055 controller
2024-03-04 Fix plus hotkey tolerances
2024-03-05 Add BG_STAT, PG_GOOD pins to CM5 GPIOs
2024-03-05 Fix rear triggers (0.5mm tolerance gap)
2024-03-08 Initial device tree draft
2024-03-10 Avoid turning the system on when battery is low
2024-03-10 Fix VBAT limit handling
2024-03-10 Simplify maths a bit
2024-03-28 Change vbat_low pin
2024-03-31 Add speaker chambers
2024-03-31 Update rear trigger pivot slots to 2.0mm thickness
2024-03-31 Add all Armbian image build stuff
2024-04-01 Reorder dts entries to minimize diff
2024-04-02 Fix malirun parameter forwarding
2024-04-15 Simplify device tree, add MAX17055 model config
2024-04-17 Reorganize code for better readability
2024-04-18 Switch shutdown signal to active low.
2024-04-18 Route shutdown signals to and from ATTiny
2024-04-18 Patch logind to respond to the "lid" button
2024-04-18 Don't wait 10 seconds if CM5 is already shut down
2024-04-23 Fix MPU6050 sleep
2024-04-26 Positive for silicone mould creation
2024-04-26 Upload silicone membrane moulds
2024-05-15 Re-arrange folders
2024-06-02 Rename Mali X11 folder, add universal malirun script
2024-06-08 Upload new v2 STLs
2024-06-27 Add final case assets
2024-06-27 Remove unnecessary file
2024-06-27 Upload final working CM5 carrier board
2024-07-01 Create LICENSE
2024-07-01 Update LICENSE
2024-07-11 Increase battery bracket to 1mm and add spacer
2024-07-18 Add magic combo for BOOTSEL
2024-07-19 Remove upstreamed stuff
2024-07-20 Remove board config, move patches to "vendor" kernel
2024-07-26 Rear intake vent
    Add cooling intake vent, reduce height of wall ribbing
2024-08-16 Fix multiaxis device product ID
2024-08-25 Swap back OTG/host lanes
2024-08-25 Upload left PCB BOM
2024-09-06 Add GET_REPORT support, fix R3 issue, increase dead zone
2024-09-09 Add 5.5" OLED datasheet
2024-09-10 Add 5.5" OLED panel timings
2024-09-10 Upload fan FFC gerbers/flex files
2024-09-15 Add Vulkan support patches
2024-09-24 Add OLED carrier board flex adapter files
2024-09-26 Add OLED panel front case
2024-10-02 Add support for Raydium RM67199, Goodix GT9886 and RetrOLED CM5
2024-10-03 Upload JLC flex production file (reference)
2024-10-11 Turn down fan speed and change freq to 25kHz
2024-12-22 Add alternative rear case with smaller exhaust vents
2025-02-25 Fix volume minus GPIO, add TPS6598x IRQ to GPIO1_D1
2025-02-25 Add main PCB latest gerbers
2025-02-25 Add left PCB gerbers
2025-02-25 Upload right PCB gerber files
2025-06-03 Rename Battery Bracket (5000mAh).stl to Battery Bracket (8000mAh).stl
2025-06-07 Upload button spacers + rotation stopper for silicone membranes
2025-06-10 Flip TPS65987D jumper clock/data (I2C)
2025-06-13 Fix HDMI ground pads
2025-06-24 Add PDF schematic (mainboard)
2025-06-24 Add assemblies (speaker housings) fused
2025-09-07 Fix placement of tab screw holes
2025-09-09 Upload carrier PCBs in gerber format
